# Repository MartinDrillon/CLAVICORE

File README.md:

# Clavicore 
## Le projet
> Piloter un clavecin à distance grâce à un clavier ergonomique

## L’instrument
La base est une copie d’une épinette italienne de 1601, vendue dans les années 70 en kit par Heugel et montée par un amateur. L’instrument a été révisé (changement des cordes, réharmonisation à la plume, rebouchage d’une fente sur la table d’harmonie). 

Le système électronique sera intégré au corps de l’instrument.

## L’automatisation

## Moitié « Moteur »
*testé et fonctionnel - photo à venir*

La carte de contrôle est basée sur un RP2354B avec un DRV8874 par solénoïde pour un contrôle bidirectionnel. Cinq cartes permettent de gérer les 49 touches du clavier. Les cartes communiquent en CAN.

### Moitié « Clavier »
*testé et fonctionnel - photo à venir*

Simple matrice de touches gérée par un Pico 2. Les événements « touches pressées » sont communiqués en CAN avec la partie « moteur » du système. Ils pourront également être transmis en MIDI à un ordinateur.

Ce projet utilisera une base de clavier ergonomique (https://github.com/MartinDrillon/IteMX3-) adaptée pour recevoir une disposition de type « Wiki-Haydn ». Une présentation plus détaillée du clavier est à venir. 

## Les solénoïdes
Les solénoïdes sont les éléments centraux du montage. Ils doivent être réalisés sur mesure. Ceux disponibles sur le marché sont :
- Trop bruyants
- Trop encombrants
- Trop puissants ou trop faibles
- Trop chers (~5 € pièce pour la référence la plus adaptée)

### Le cahier des charges
- Bobine de 28 mm x 15 mm Ø max, intégrée au corps du clavecin, pour être invisible et conserver la possibilité de jouer normalement.   
- Noyau constitué d’un aimant néodyme de 13 mm x 6 mm Ø N48 fixé sous la touche.
- Alimentation en 24 volts, courant de 2 à 3 ampères
    - Au-delà, la chauffe de la bobine et la puissance nécessaire à un accord deviennent trop importantes
    - En deçà, la force n’est pas suffisante ou le nombre de spires devient trop élevé
- Fil d’un diamètre de 0,3 à 0,4 mm. 
    - Au-delà, la quantité de cuivre par bobine devient trop importante (coût, encombrement, bobinage complexe).
    - En deçà, la force est trop faible ou la chauffe est trop élevée. 

### Le prototype

Le mandrin est imprimé en 3D avec une résine industrielle résistante à de hautes températures. Sa section est ovoïde pour permettre le mouvement de l’aimant (qui n’est pas parfaitement vertical, la touche s’enfonçant avec un angle) tout en minimisant l’écart avec les spires. La paroi intérieure ne fait que 0,8mm d’épaisseur. Ce prototype tire environ 3,1 ampères pour 12 couches et un fil de 0,35mm. 

La force max estimée est de 3N, soit environ le double de ce qui est nécessaire au pincement d’une corde. Cette marge permet de garantir la réactivité du système et de compenser la perte de puissance causée par l’échauffement. La force exacte appliquée est controllé en PWM (par exemple 100% pour le pincement, puis très limité pour le maintien de la corde). Ces éléments sont en cours de calibration.

## L’état d’avancement 

Les cartes sont fonctionnelles. Les derniers ajustements firmware et de calibration des solénoïdes sont en cours avant l’assemblage de l’ensemble de l’instrument. Les résultats obtenus sur les premières touches assemblées sont très satisfaisants. 

- [X] Génération d’un script Magpylib pour réaliser un premier dimensionnement des solénoïdes 
- [X] Modélisation 3D de l’instrument
- [X] Conception et impression 3D du corps de la bobine intégré sous les touches
- [X] Premier test concluant avec un fil de 0,4 mm - 2 ampères - 24 volts
- [X] Conception et assemblage des cartes de pilotage pour l’ensemble du clavecin 
- [X] Conception et assemblage du clavier ergonomique 
- [ ] Programmation de l’ensemble *en cours*
- [ ] Calibration du profil d’activation des solénoïdes *en cours*
- [ ] Réalisation artisanale de 50 bobines homogènes et installation du système ! *en cours*

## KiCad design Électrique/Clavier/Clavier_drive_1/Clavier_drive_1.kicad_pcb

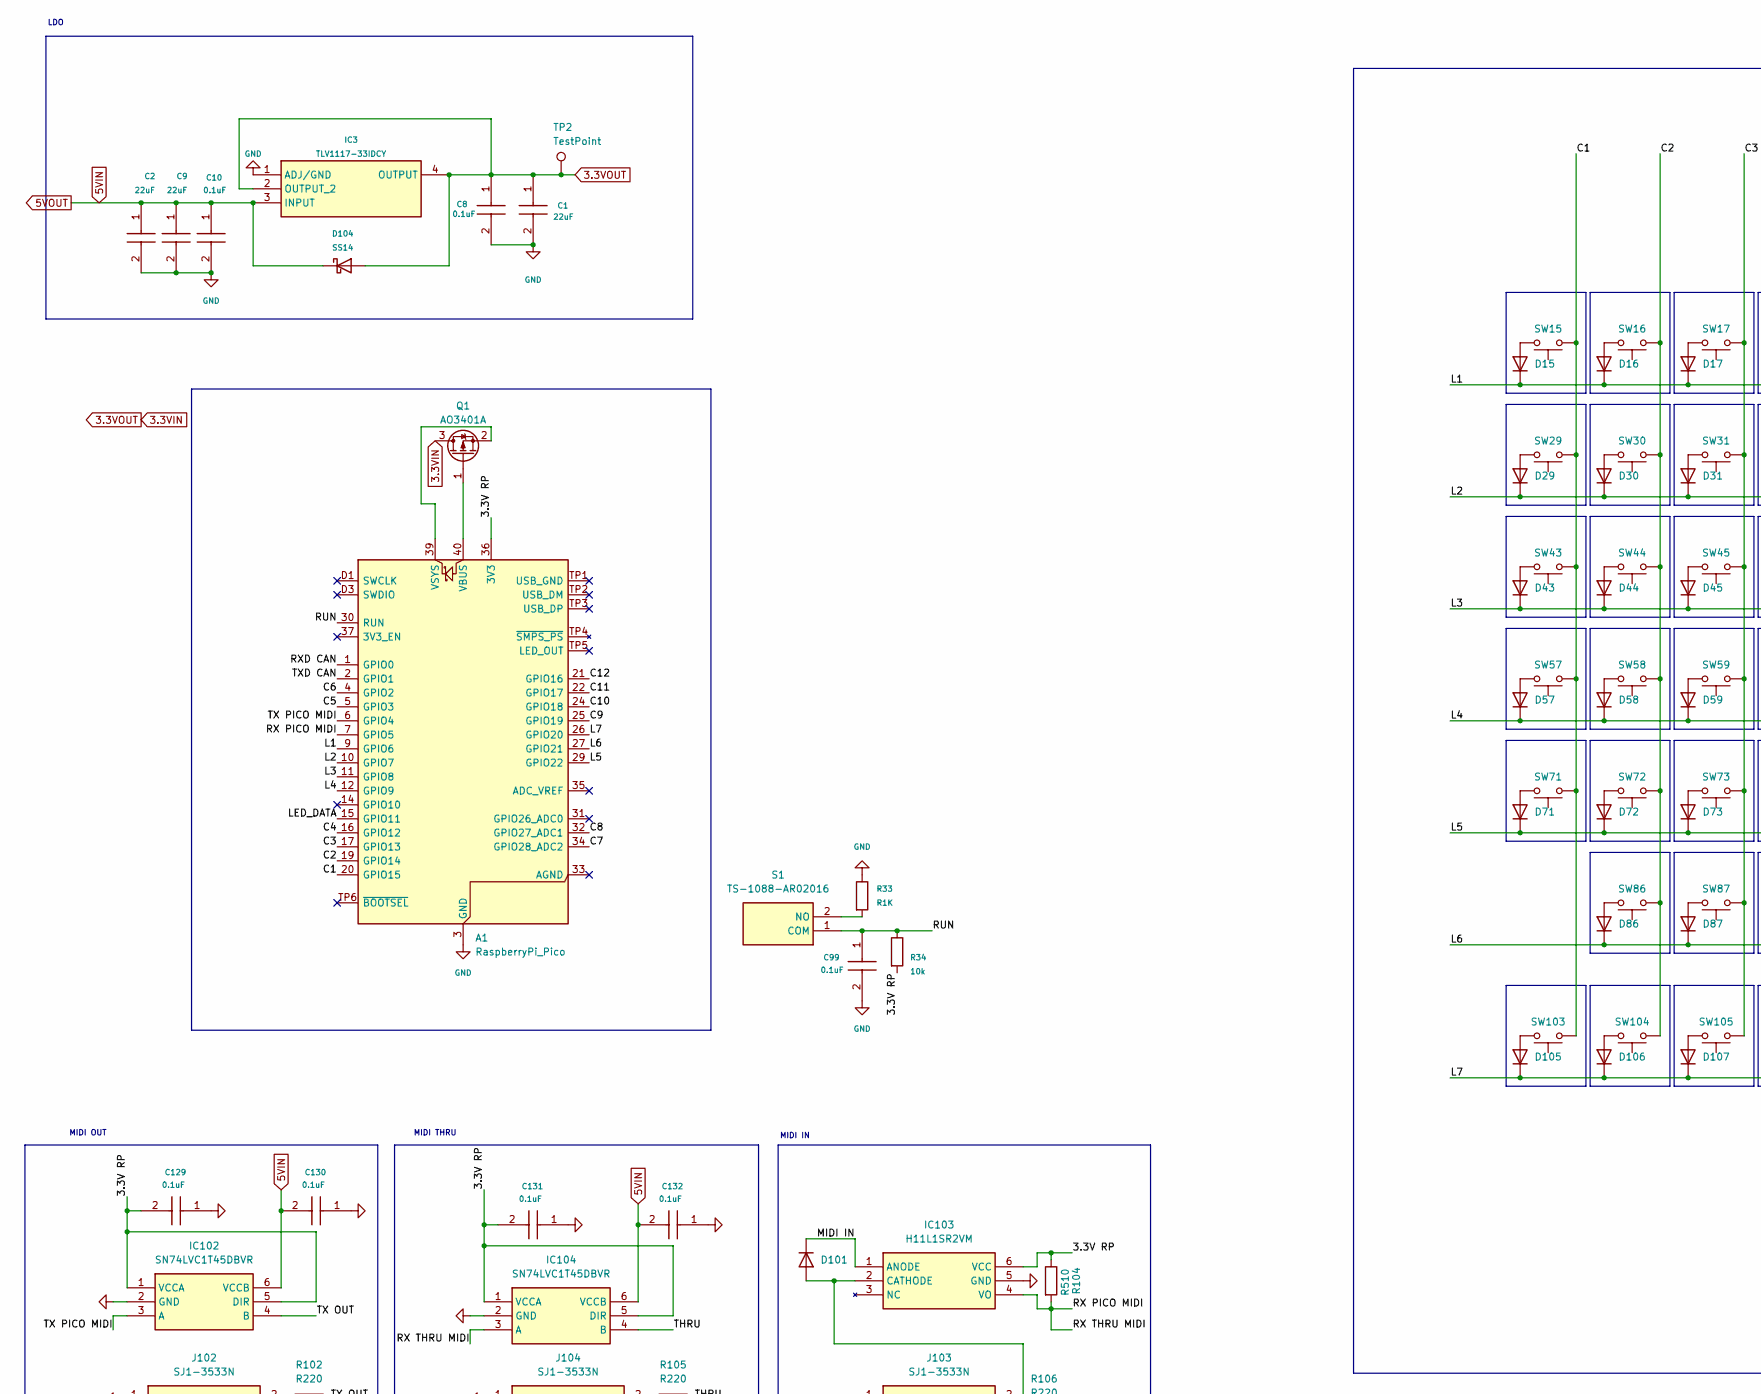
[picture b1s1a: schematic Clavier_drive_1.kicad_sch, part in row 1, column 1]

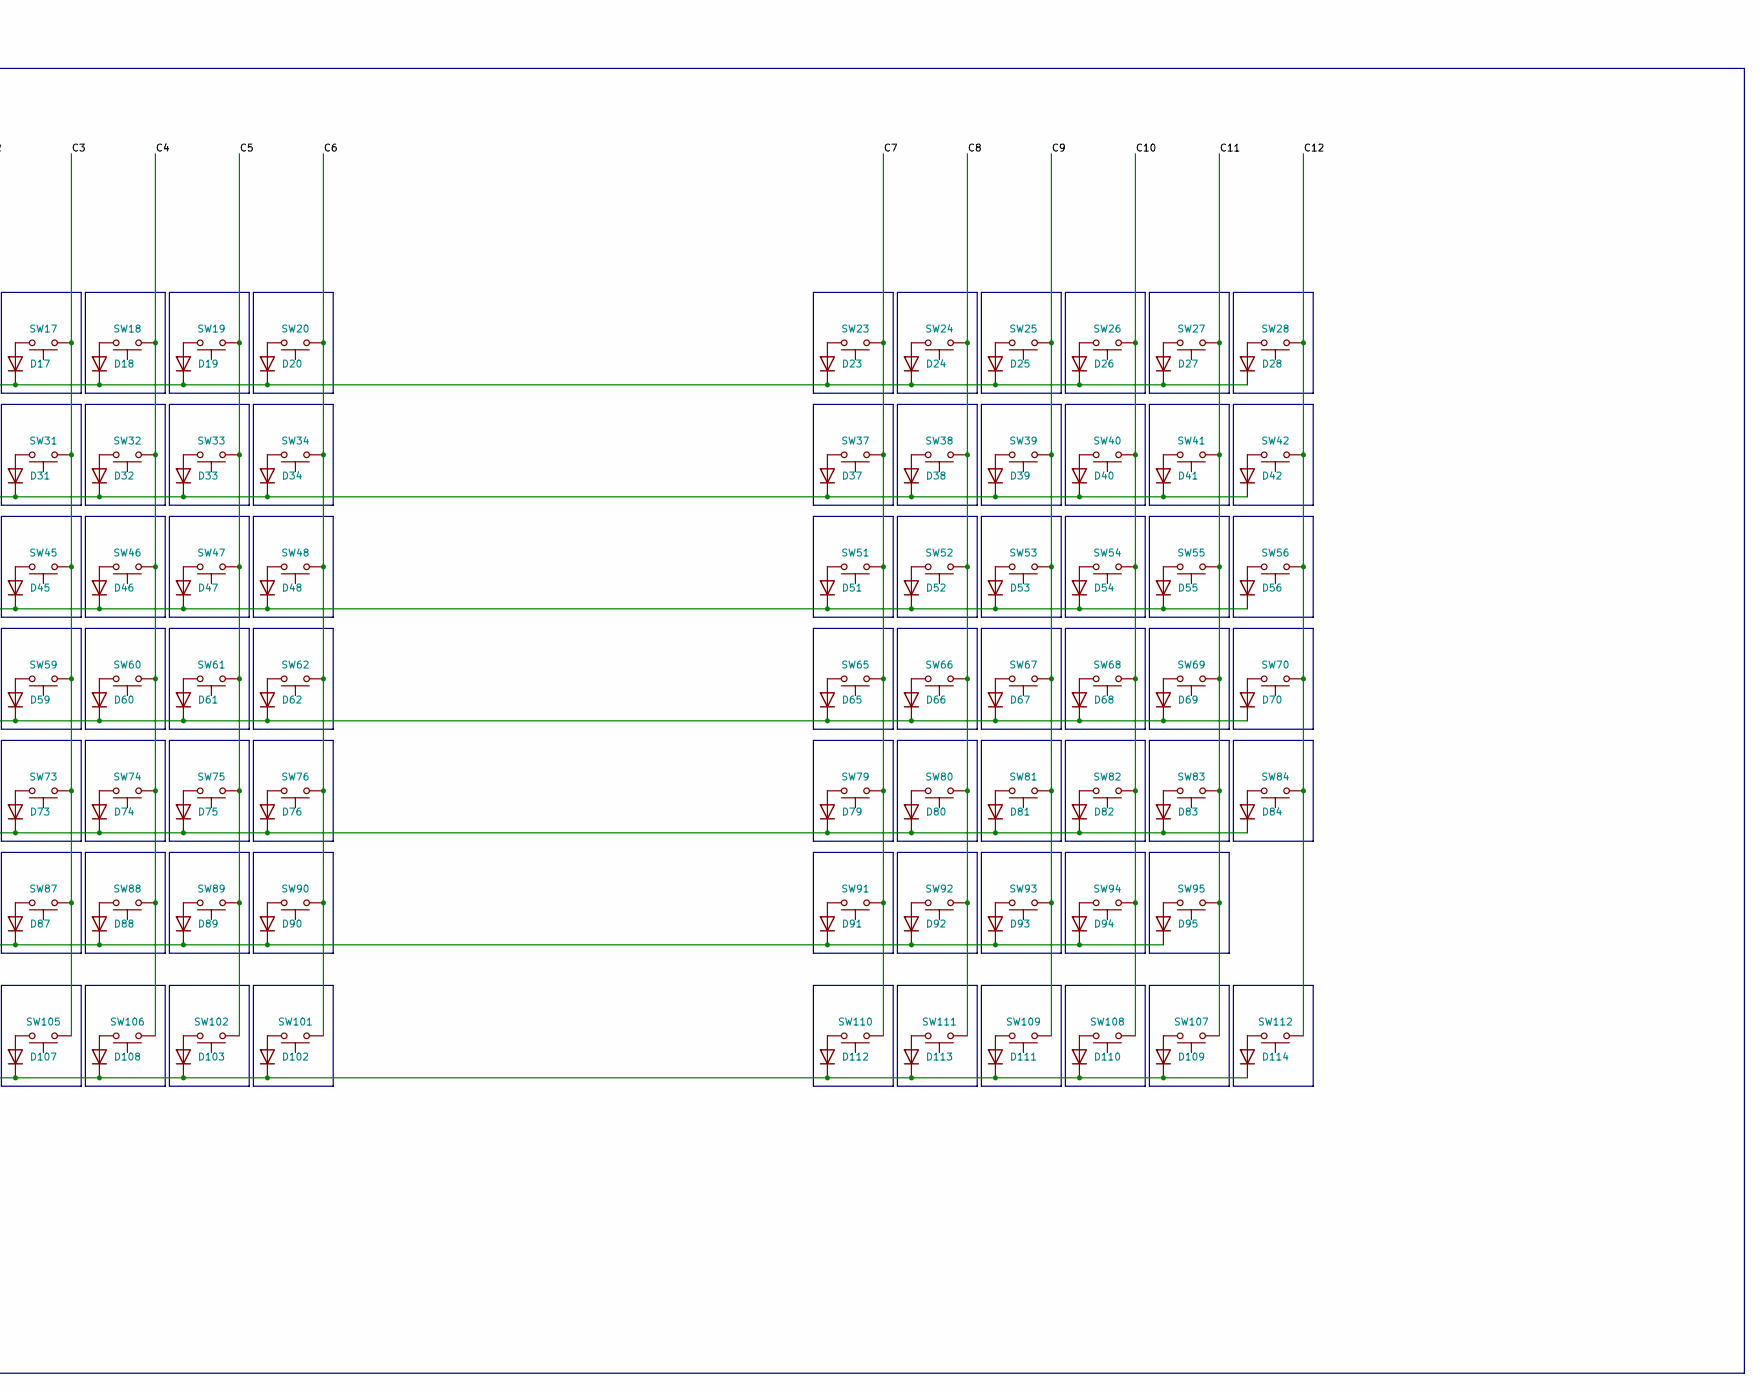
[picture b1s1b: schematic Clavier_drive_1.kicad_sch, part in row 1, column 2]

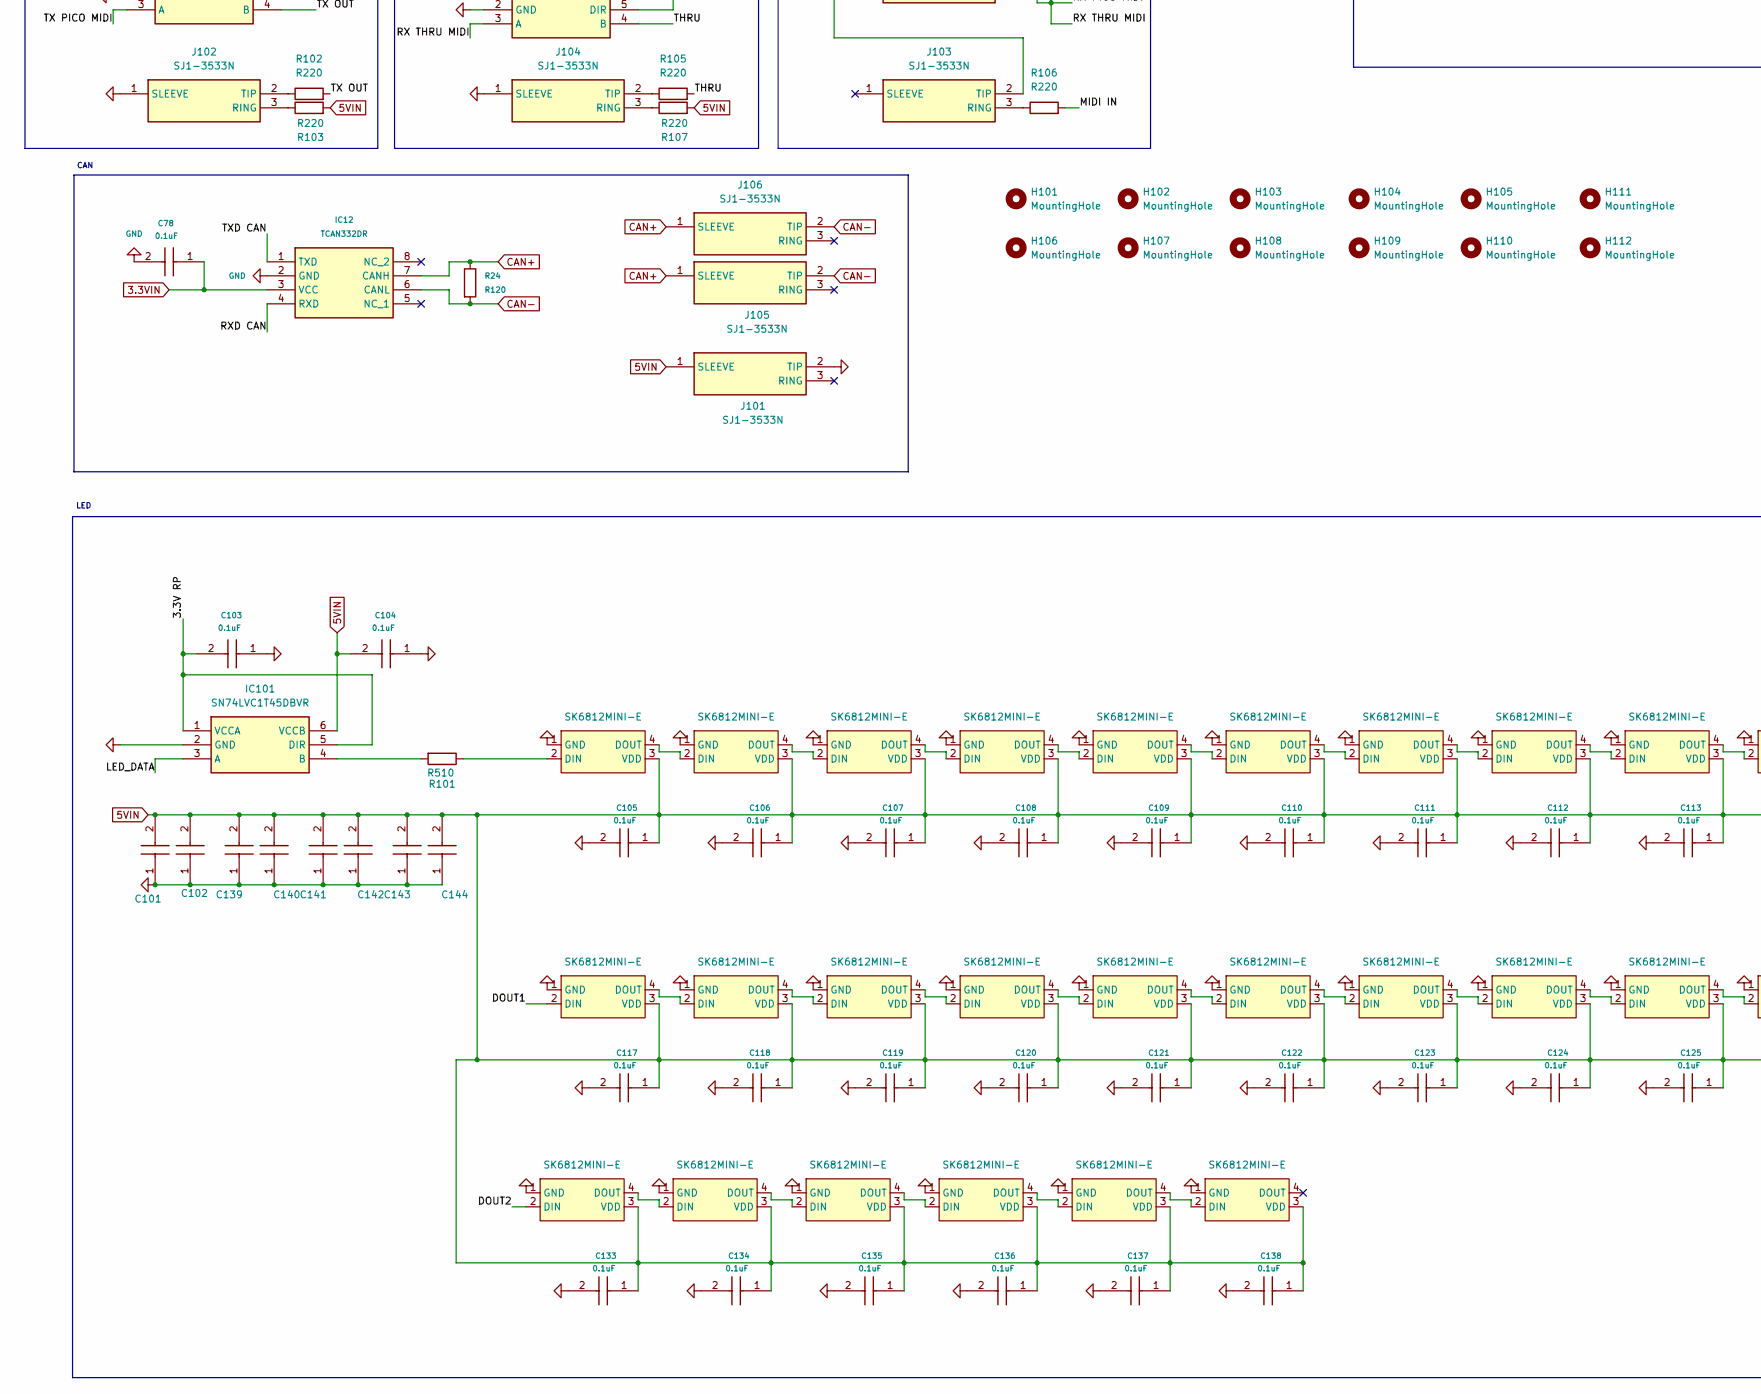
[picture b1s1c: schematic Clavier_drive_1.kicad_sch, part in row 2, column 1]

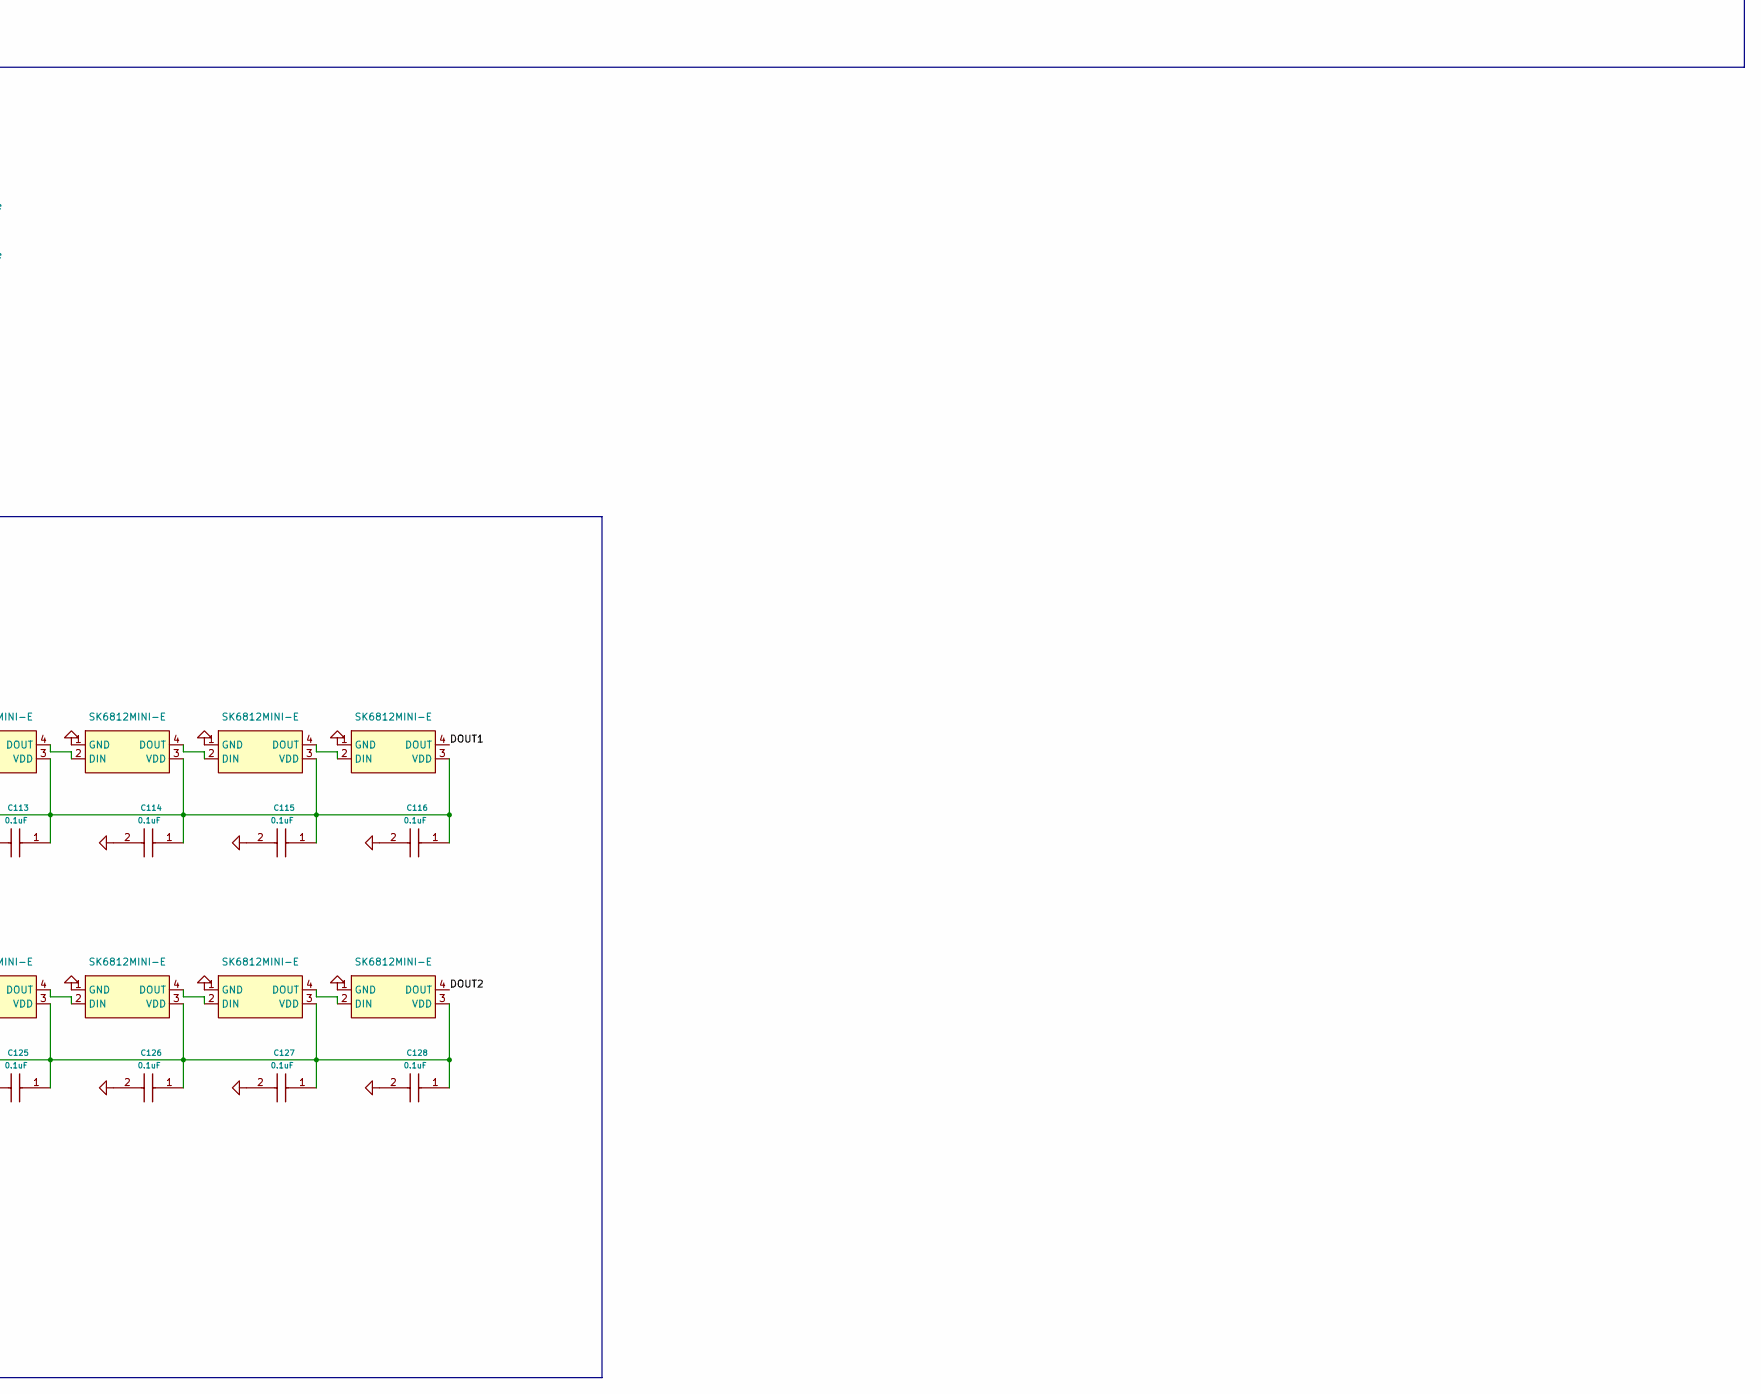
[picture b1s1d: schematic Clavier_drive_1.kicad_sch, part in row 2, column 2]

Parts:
A1: RaspberryPi_Pico; RaspberryPi_Pico_SMD
C1, C2, C9: 22uF; C_1206_3216Metric; Mouser Part Number 187-CL31A226KAHNNNE
C8, C10, C78, C99, C103, C104, C105, C106, C107, C108, C109, C110, C111, C112, C113, C114, C115, C116, C117, C118, C119, C120, C121, C122, C123, C124, C125, C126, C127, C128, C129, C130, C131, C132, C133, C134, C135, C136, C137, C138: 0.1uF; C_0402_1005Metric; Mouser Part Number 603-CC603KRX7R9BB104
C101, C102, C139, C140, C141, C142, C143, C144: CL31A476MPHNNNE; CAPC3216X180N; Mouser Part Number 187-CL31A476MPHNNNE
D15, D16, D17, D18, D19, D20, D23, D24, D25, D26, D27, D28, D29, D30, D31, D32, D33, D34, D37, D38, D39, D40, D41, D42, D43, D44, D45, D46, D47, D48, D51, D52, D53, D54, D55, D56, D57, D58, D59, D60, D61, D62, D65, D66, D67, D68, D69, D70, D71, D72, D73, D74, D75, D76, D79, D80, D81, D82, D83, D84, D86, D87, D88, D89, D90, D91, D92, D93, D94, D95, D101, D102, D103, D105, D106, D107, D108, D109, D110, D111, D112, D113, D114: 1N4148W; D_SOD-123
D104: SS14; D_SMA
H101, H102, H103, H104, H105, H106, H107, H108, H109, H110, H111, H112: MountingHole; MountingHole_3.2mm_M3_DIN965
IC3: TLV1117-33IDCY; SOT230P700X180-4N; Mouser Part Number 595-TLV1117-33IDCY
IC12: TCAN332DR; SOIC127P600X175-8N; Mouser Part Number 595-TCAN332DR
IC101, IC102, IC104: SN74LVC1T45DBVR; SOT95P280X145-6N; Mouser Part Number 595-SN74LVC1T45DBVR
IC103: H11L1SR2VM; Mouser Part Number 512-H11L1SR2VM
J101, J102, J103, J104, J105, J106: SJ1-3533N; SJ13533N; Mouser Part Number 490-SJ1-3533N
LED101, LED102, LED103, LED104, LED105, LED106, LED107, LED108, LED109, LED110, LED111, LED112, LED113, LED114, LED115, LED116, LED117, LED118, LED119, LED120, LED121, LED122, LED123, LED124, LED125, LED126, LED127, LED128, LED129, LED130: SK6812MINI-E; LED-SMD_4P-L3.2-W2.8-LS5.9_SK6812MINI-E; MPN SK6812MINI-E; LCSC Part C5149201
Q1: AO3401A; SOT-23
R24: R120; R_0603_1608Metric
R33: R1K; R_0603_1608Metric
R34: 10k; R_0603_1608Metric
R101, R104: R510; R_0603_1608Metric
R102, R103, R105, R106, R107: R220; R_0603_1608Metric
S1: TS-1088-AR02016; TS1088AR02016; Manufacturer_Part_Number TS-1088-AR02016
SW15, SW16, SW17, SW18, SW19, SW20, SW23, SW24, SW25, SW26, SW27, SW28, SW29, SW30, SW31, SW32, SW33, SW34, SW37, SW38, SW39, SW40, SW41, SW42, SW43, SW44, SW45, SW46, SW47, SW48, SW51, SW52, SW53, SW54, SW55, SW56, SW57, SW58, SW59, SW60, SW61, SW62, SW65, SW66, SW67, SW68, SW69, SW70, SW71, SW72, SW73, SW74, SW75, SW76, SW79, SW80, SW81, SW82, SW83, SW84, SW86, SW87, SW88, SW89, SW90, SW91, SW92, SW93, SW94, SW95, SW101, SW102, SW103, SW104, SW105, SW106, SW107, SW108, SW109, SW110, SW111, SW112: Switch; SW_MX_HS_CPG151101S11_1u
TP2: TestPoint; TestPoint_Pad_D1.0mm_Silkless

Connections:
3.3VIN: C1.1, C8.1, C78.1, D104.2 (A), IC3.2 (OUTPUT_2), IC3.4 (OUTPUT), IC12.3 (VCC), Q1.3 (D), TP2.1 (1_1)
5VIN: C2.1, C9.1, C10.1, C101.2, C102.2, C104.2, C105.1, C106.1, C107.1, C108.1, C109.1, C110.1, C111.1, C112.1, C113.1, C114.1, C115.1, C116.1, C117.1, C118.1, C119.1, C120.1, C121.1, C122.1, C123.1, C124.1, C125.1, C126.1, C127.1, C128.1, C130.2, C132.2, C133.1, C134.1, C135.1, C136.1, C137.1, C138.1, C139.2, C140.2, C141.2, C142.2, C143.2, C144.2, D104.1 (K), IC3.3 (INPUT), IC101.6 (VCCB), IC102.6 (VCCB), IC104.6 (VCCB), J101.1 (SLEEVE), LED101.3 (VDD), LED102.3 (VDD), LED103.3 (VDD), LED104.3 (VDD), LED105.3 (VDD), LED106.3 (VDD), LED107.3 (VDD), LED108.3 (VDD), LED109.3 (VDD), LED110.3 (VDD), LED111.3 (VDD), LED112.3 (VDD), LED113.3 (VDD), LED114.3 (VDD), LED115.3 (VDD), LED116.3 (VDD), LED117.3 (VDD), LED118.3 (VDD), LED119.3 (VDD), LED120.3 (VDD), LED121.3 (VDD), LED122.3 (VDD), LED123.3 (VDD), LED124.3 (VDD), LED125.3 (VDD), LED126.3 (VDD), LED127.3 (VDD), LED128.3 (VDD), LED129.3 (VDD), LED130.3 (VDD), R103.2, R107.2
/3.3V RP: A1.36 (3V3), C103.2, C129.2, C131.2, IC101.1 (VCCA), IC101.5 (DIR), IC102.1 (VCCA), IC102.5 (DIR), IC103.6 (VCC), IC104.1 (VCCA), IC104.5 (DIR), R34.2, R104.1
/C1: A1.20 (GPIO15), SW15.1, SW29.1, SW43.1, SW57.1, SW71.1, SW103.1
/C2: A1.19 (GPIO14), SW16.1, SW30.1, SW44.1, SW58.1, SW72.1, SW86.1, SW104.1
/C3: A1.17 (GPIO13), SW17.1, SW31.1, SW45.1, SW59.1, SW73.1, SW87.1, SW105.1
/C4: A1.16 (GPIO12), SW18.1, SW32.1, SW46.1, SW60.1, SW74.1, SW88.1, SW106.1
/C5: A1.5 (GPIO3), SW19.1, SW33.1, SW47.1, SW61.1, SW75.1, SW89.1, SW102.1
/C6: A1.4 (GPIO2), SW20.1, SW34.1, SW48.1, SW62.1, SW76.1, SW90.1, SW101.1
/C7: A1.34 (GPIO28_ADC2), SW23.1, SW37.1, SW51.1, SW65.1, SW79.1, SW91.1, SW110.1
/C8: A1.32 (GPIO27_ADC1), SW24.1, SW38.1, SW52.1, SW66.1, SW80.1, SW92.1, SW111.1
/C9: A1.25 (GPIO19), SW25.1, SW39.1, SW53.1, SW67.1, SW81.1, SW93.1, SW109.1
/C10: A1.24 (GPIO18), SW26.1, SW40.1, SW54.1, SW68.1, SW82.1, SW94.1, SW108.1
/C11: A1.22 (GPIO17), SW27.1, SW41.1, SW55.1, SW69.1, SW83.1, SW95.1, SW107.1
/C12: A1.21 (GPIO16), SW28.1, SW42.1, SW56.1, SW70.1, SW84.1, SW112.1
/DOUT1: LED112.4 (DOUT), LED113.2 (DIN)
/DOUT2: LED124.4 (DOUT), LED125.2 (DIN)
/L1: A1.9 (GPIO6), D15.1 (K), D16.1 (K), D17.1 (K), D18.1 (K), D19.1 (K), D20.1 (K), D23.1 (K), D24.1 (K), D25.1 (K), D26.1 (K), D27.1 (K), D28.1 (K)
/L2: A1.10 (GPIO7), D29.1 (K), D30.1 (K), D31.1 (K), D32.1 (K), D33.1 (K), D34.1 (K), D37.1 (K), D38.1 (K), D39.1 (K), D40.1 (K), D41.1 (K), D42.1 (K)
/L3: A1.11 (GPIO8), D43.1 (K), D44.1 (K), D45.1 (K), D46.1 (K), D47.1 (K), D48.1 (K), D51.1 (K), D52.1 (K), D53.1 (K), D54.1 (K), D55.1 (K), D56.1 (K)
/L4: A1.12 (GPIO9), D57.1 (K), D58.1 (K), D59.1 (K), D60.1 (K), D61.1 (K), D62.1 (K), D65.1 (K), D66.1 (K), D67.1 (K), D68.1 (K), D69.1 (K), D70.1 (K)
/L5: A1.29 (GPIO22), D71.1 (K), D72.1 (K), D73.1 (K), D74.1 (K), D75.1 (K), D76.1 (K), D79.1 (K), D80.1 (K), D81.1 (K), D82.1 (K), D83.1 (K), D84.1 (K)
/L6: A1.27 (GPIO21), D86.1 (K), D87.1 (K), D88.1 (K), D89.1 (K), D90.1 (K), D91.1 (K), D92.1 (K), D93.1 (K), D94.1 (K), D95.1 (K)
/L7: A1.26 (GPIO20), D102.1 (K), D103.1 (K), D105.1 (K), D106.1 (K), D107.1 (K), D108.1 (K), D109.1 (K), D110.1 (K), D111.1 (K), D112.1 (K), D113.1 (K), D114.1 (K)
/LED_DATA: A1.15 (GPIO11), IC101.3 (A)
/MIDI IN: D101.1 (K), IC103.1 (ANODE), R106.2
/RUN: A1.30 (RUN), C99.1, R34.1, S1.1 (COM)
/RXD CAN: A1.1 (GPIO0), IC12.4 (RXD)
/THRU: IC104.4 (B), R105.2
/TX OUT: IC102.4 (B), R102.2
/TX PICO MIDI: A1.6 (GPIO4), IC102.3 (A)
/TXD CAN: A1.2 (GPIO1), IC12.1 (TXD)
/ RX PICO MIDI: A1.7 (GPIO5), IC103.4 (VO), IC104.3 (A), R104.2
CAN+: IC12.7 (CANH), J105.1 (SLEEVE), J106.1 (SLEEVE), R24.1
CAN-: IC12.6 (CANL), J105.2 (TIP), J106.2 (TIP), R24.2
GND: A1.3 (GND), A1.8 (GND), A1.13 (GND), A1.18 (GND), A1.23 (GND), A1.28 (GND), A1.38 (GND), A1.D2 (GND), C1.2, C2.2, C8.2, C9.2, C10.2, C78.2, C99.2, C101.1, C102.1, C103.1, C104.1, C105.2, C106.2, C107.2, C108.2, C109.2, C110.2, C111.2, C112.2, C113.2, C114.2, C115.2, C116.2, C117.2, C118.2, C119.2, C120.2, C121.2, C122.2, C123.2, C124.2, C125.2, C126.2, C127.2, C128.2, C129.1, C130.1, C131.1, C132.1, C133.2, C134.2, C135.2, C136.2, C137.2, C138.2, C139.1, C140.1, C141.1, C142.1, C143.1, C144.1, IC3.1 (ADJ/GND), IC12.2 (GND), IC101.2 (GND), IC102.2 (GND), IC103.5 (GND), IC104.2 (GND), J101.2 (TIP), J102.1 (SLEEVE), J104.1 (SLEEVE), LED101.1 (GND), LED102.1 (GND), LED103.1 (GND), LED104.1 (GND), LED105.1 (GND), LED106.1 (GND), LED107.1 (GND), LED108.1 (GND), LED109.1 (GND), LED110.1 (GND), LED111.1 (GND), LED112.1 (GND), LED113.1 (GND), LED114.1 (GND), LED115.1 (GND), LED116.1 (GND), LED117.1 (GND), LED118.1 (GND), LED119.1 (GND), LED120.1 (GND), LED121.1 (GND), LED122.1 (GND), LED123.1 (GND), LED124.1 (GND), LED125.1 (GND), LED126.1 (GND), LED127.1 (GND), LED128.1 (GND), LED129.1 (GND), LED130.1 (GND), R33.1
unnamed: A1.40 (VBUS), Q1.1 (G)
unnamed: A1.39 (VSYS), Q1.2 (S)
unnamed: D15.2 (A), SW15.2
unnamed: D16.2 (A), SW16.2
unnamed: D17.2 (A), SW17.2
unnamed: D18.2 (A), SW18.2
unnamed: D19.2 (A), SW19.2
unnamed: D20.2 (A), SW20.2
unnamed: D23.2 (A), SW23.2
unnamed: D24.2 (A), SW24.2
unnamed: D25.2 (A), SW25.2
unnamed: D26.2 (A), SW26.2
unnamed: D27.2 (A), SW27.2
unnamed: D28.2 (A), SW28.2
unnamed: D29.2 (A), SW29.2
unnamed: D30.2 (A), SW30.2
unnamed: D31.2 (A), SW31.2
unnamed: D32.2 (A), SW32.2
unnamed: D33.2 (A), SW33.2
unnamed: D34.2 (A), SW34.2
unnamed: D37.2 (A), SW37.2
unnamed: D38.2 (A), SW38.2
unnamed: D39.2 (A), SW39.2
unnamed: D40.2 (A), SW40.2
unnamed: D41.2 (A), SW41.2
unnamed: D42.2 (A), SW42.2
unnamed: D43.2 (A), SW43.2
unnamed: D44.2 (A), SW44.2
unnamed: D45.2 (A), SW45.2
unnamed: D46.2 (A), SW46.2
unnamed: D47.2 (A), SW47.2
unnamed: D48.2 (A), SW48.2
unnamed: D51.2 (A), SW51.2
unnamed: D52.2 (A), SW52.2
unnamed: D53.2 (A), SW53.2
unnamed: D54.2 (A), SW54.2
unnamed: D55.2 (A), SW55.2
unnamed: D56.2 (A), SW56.2
unnamed: D57.2 (A), SW57.2
unnamed: D58.2 (A), SW58.2
unnamed: D59.2 (A), SW59.2
unnamed: D60.2 (A), SW60.2
unnamed: D61.2 (A), SW61.2
unnamed: D62.2 (A), SW62.2
unnamed: D65.2 (A), SW65.2
unnamed: D66.2 (A), SW66.2
unnamed: D67.2 (A), SW67.2
unnamed: D68.2 (A), SW68.2
unnamed: D69.2 (A), SW69.2
unnamed: D70.2 (A), SW70.2
unnamed: D71.2 (A), SW71.2
unnamed: D72.2 (A), SW72.2
unnamed: D73.2 (A), SW73.2
unnamed: D74.2 (A), SW74.2
unnamed: D75.2 (A), SW75.2
unnamed: D76.2 (A), SW76.2
unnamed: D79.2 (A), SW79.2
unnamed: D80.2 (A), SW80.2
unnamed: D81.2 (A), SW81.2
unnamed: D82.2 (A), SW82.2
unnamed: D83.2 (A), SW83.2
unnamed: D84.2 (A), SW84.2
unnamed: D86.2 (A), SW86.2
unnamed: D87.2 (A), SW87.2
unnamed: D88.2 (A), SW88.2
unnamed: D89.2 (A), SW89.2
unnamed: D90.2 (A), SW90.2
unnamed: D91.2 (A), SW91.2
unnamed: D92.2 (A), SW92.2
unnamed: D93.2 (A), SW93.2
unnamed: D94.2 (A), SW94.2
unnamed: D95.2 (A), SW95.2
unnamed: D101.2 (A), IC103.2 (CATHODE), J103.2 (TIP)
unnamed: D102.2 (A), SW101.2
unnamed: D103.2 (A), SW102.2
unnamed: D105.2 (A), SW103.2
unnamed: D106.2 (A), SW104.2
unnamed: D107.2 (A), SW105.2
unnamed: D108.2 (A), SW106.2
unnamed: D109.2 (A), SW107.2
unnamed: D110.2 (A), SW108.2
unnamed: D111.2 (A), SW109.2
unnamed: D112.2 (A), SW110.2
unnamed: D113.2 (A), SW111.2
unnamed: D114.2 (A), SW112.2
unnamed: IC101.4 (B), R101.2
unnamed: J102.3 (RING), R103.1
unnamed: J102.2 (TIP), R102.1
unnamed: J103.3 (RING), R106.1
unnamed: J104.3 (RING), R107.1
unnamed: J104.2 (TIP), R105.1
unnamed: LED101.2 (DIN), R101.1
unnamed: LED101.4 (DOUT), LED102.2 (DIN)
unnamed: LED102.4 (DOUT), LED103.2 (DIN)
unnamed: LED103.4 (DOUT), LED104.2 (DIN)
unnamed: LED104.4 (DOUT), LED105.2 (DIN)
unnamed: LED105.4 (DOUT), LED106.2 (DIN)
unnamed: LED106.4 (DOUT), LED107.2 (DIN)
unnamed: LED107.4 (DOUT), LED108.2 (DIN)
unnamed: LED108.4 (DOUT), LED109.2 (DIN)
unnamed: LED109.4 (DOUT), LED110.2 (DIN)
unnamed: LED110.4 (DOUT), LED111.2 (DIN)
unnamed: LED111.4 (DOUT), LED112.2 (DIN)
unnamed: LED113.4 (DOUT), LED114.2 (DIN)
unnamed: LED114.4 (DOUT), LED115.2 (DIN)
unnamed: LED115.4 (DOUT), LED116.2 (DIN)
unnamed: LED116.4 (DOUT), LED117.2 (DIN)
unnamed: LED117.4 (DOUT), LED118.2 (DIN)
unnamed: LED118.4 (DOUT), LED119.2 (DIN)
unnamed: LED119.4 (DOUT), LED120.2 (DIN)
unnamed: LED120.4 (DOUT), LED121.2 (DIN)
unnamed: LED121.4 (DOUT), LED122.2 (DIN)
unnamed: LED122.4 (DOUT), LED123.2 (DIN)
unnamed: LED123.4 (DOUT), LED124.2 (DIN)
unnamed: LED125.4 (DOUT), LED126.2 (DIN)
unnamed: LED126.4 (DOUT), LED127.2 (DIN)
unnamed: LED127.4 (DOUT), LED128.2 (DIN)
unnamed: LED128.4 (DOUT), LED129.2 (DIN)
unnamed: LED129.4 (DOUT), LED130.2 (DIN)
unnamed: R33.2, S1.2 (NO)

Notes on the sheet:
MIDI OUT
LED
MIDI IN
CAN
LDO
MIDI THRU

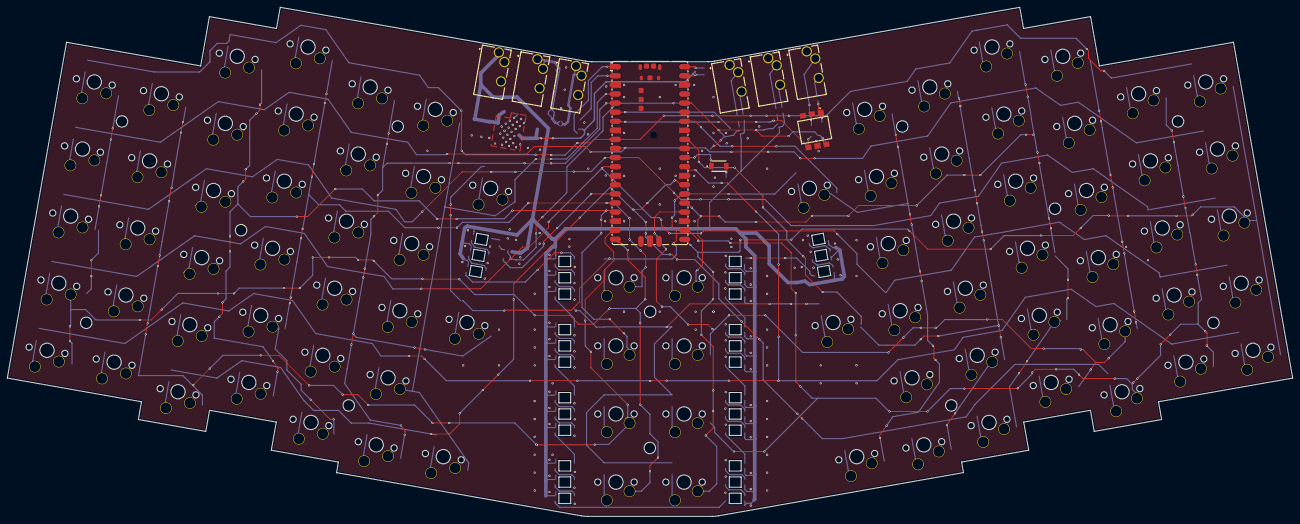
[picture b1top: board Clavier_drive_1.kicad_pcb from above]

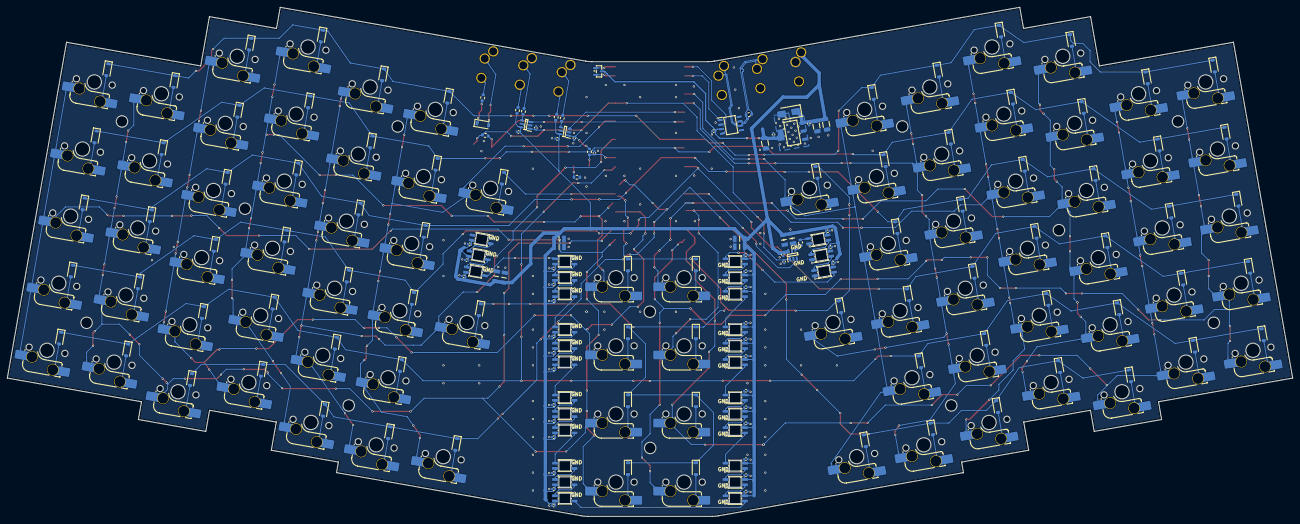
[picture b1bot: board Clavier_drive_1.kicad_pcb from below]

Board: 2 copper layers, 359.4 x 142.3 mm, 285 parts (264 on the bottom side), 156 nets.

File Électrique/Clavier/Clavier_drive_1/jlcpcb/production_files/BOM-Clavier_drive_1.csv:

Comment,Designator,Footprint,LCSC,Quantity
0.1uF,"C10,C103,C104,C105,C106,C107,C108,C109,C110,C111,C112,C113,C114,C115,C116,C117,C118,C119,C120,C121,C122,C123,C124,C125,C126,C127,C128,C129,C130,C131,C132,C133,C134,C135,C136,C137,C138,C78,C8,C99",C_0402_1005Metric,C307331,40
10k,R34,R_0603_1608Metric,C25804,1
1N4148W,"D101,D102,D103,D105,D106,D107,D108,D109,D110,D111,D112,D113,D114,D15,D16,D17,D18,D19,D20,D23,D24,D25,D26,D27,D28,D29,D30,D31,D32,D33,D34,D37,D38,D39,D40,D41,D42,D43,D44,D45,D46,D47,D48,D51,D52,D53,D54,D55,D56,D57,D58,D59,D60,D61,D62,D65,D66,D67,D68,D69,D70,D71,D72,D73,D74,D75,D76,D79,D80,D81,D82,D83,D84,D86,D87,D88,D89,D90,D91,D92,D93,D94,D95",D_SOD-123,C81598,83
22uF,"C1,C2,C9",C_1206_3216Metric,C12891,3
AO3401A,Q1,SOT-23,C15127,1
CL31A476MPHNNNE,"C101,C102,C139,C140,C141,C142,C143,C144",CAPC3216X180N,C96123,8
H11L1SR2VM,IC103,H11L1SR2VM,C274632,1
R120,R24,R_0603_1608Metric,C22787,1
R1K,R33,R_0603_1608Metric,C21190,1
R220,"R102,R103,R105,R106,R107",R_0603_1608Metric,C22962,5
R510,"R101,R104",R_0603_1608Metric,C23193,2
SJ1-3533N,"J101,J102,J103,J104,J105,J106",SJ13533N,C4992459,6
SK6812MINI-E,"LED101,LED102,LED103,LED104,LED105,LED106,LED107,LED108,LED109,LED110,LED111,LED112,LED113,LED114,LED115,LED116,LED117,LED118,LED119,LED120,LED121,LED122,LED123,LED124,LED125,LED126,LED127,LED128,LED129,LED130",LED-SMD_4P-L3.2-W2.8-LS5.9_SK6812MINI-E,C5149201,30
SN74LVC1T45DBVR,"IC101,IC102,IC104",SOT95P280X145-6N,C7843,3
SS14,D104,D_SMA,C2480,1
Switch,"SW101,SW102,SW103,SW104,SW105,SW106,SW107,SW108,SW109,SW110,SW111,SW112,SW15,SW16,SW17,SW18,SW19,SW20,SW23,SW24,SW25,SW26,SW27,SW28,SW29,SW30,SW31,SW32,SW33,SW34,SW37,SW38,SW39,SW40,SW41,SW42,SW43,SW44,SW45,SW46,SW47,SW48,SW51,SW52,SW53,SW54,SW55,SW56,SW57,SW58,SW59,SW60,SW61,SW62,SW65,SW66,SW67,SW68,SW69,SW70,SW71,SW72,SW73,SW74,SW75,SW76,SW79,SW80,SW81,SW82,SW83,SW84,SW86,SW87,SW88,SW89,SW90,SW91,SW92,SW93,SW94,SW95",SW_MX_HS_CPG151101S11_1u,C41430893,82
TCAN332DR,IC12,SOIC127P600X175-8N,C73651,1
TLV1117-33IDCY,IC3,SOT230P700X180-4N,C37359,1
TS-1088-AR02016,S1,TS1088AR02016,C720477,1
RaspberryPi_Pico,A1,RaspberryPi_Pico_SMD,,1
